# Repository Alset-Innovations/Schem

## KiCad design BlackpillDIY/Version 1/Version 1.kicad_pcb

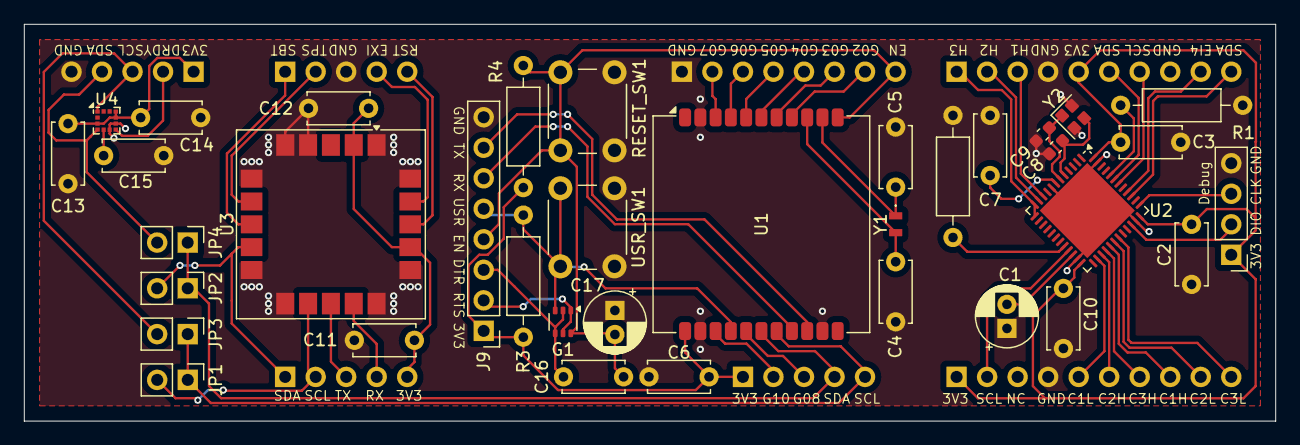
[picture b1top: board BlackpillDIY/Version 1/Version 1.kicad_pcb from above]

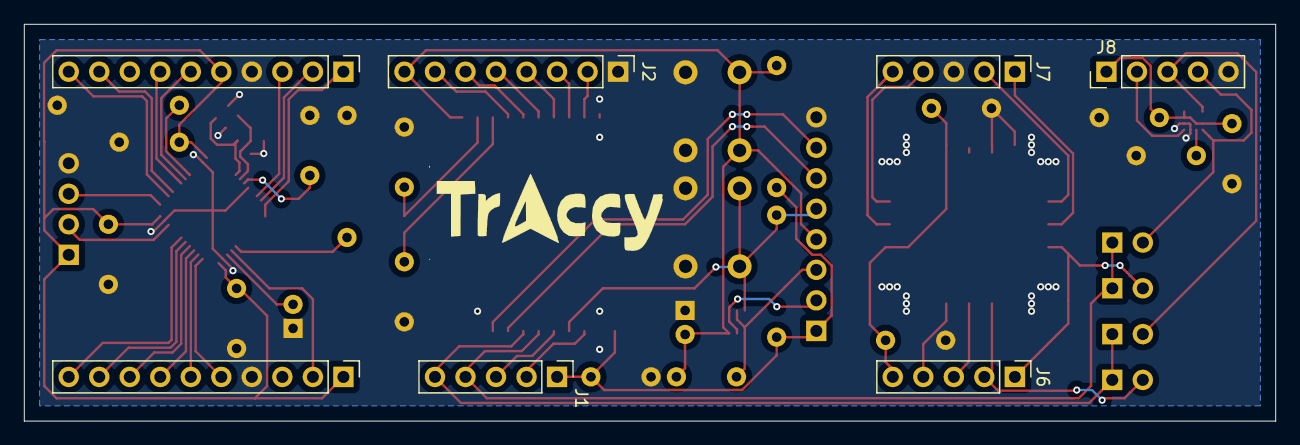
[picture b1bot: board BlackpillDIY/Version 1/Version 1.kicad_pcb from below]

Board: 2 copper layers, 104.1 x 33.0 mm, 43 parts (7 on the bottom side), 57 nets.

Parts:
C1, C2, C3, C6, C7, C11, C12, C13, C14, C15, C16: 100n; C_Disc_D5.0mm_W2.5mm_P5.00mm
C4, C5: 22p; C_Disc_D5.0mm_W2.5mm_P5.00mm
C8, C9: 12p; C_0603_1608Metric
C10, C17: 2.2u; CP_Radial_D5.0mm_P2.00mm
G1: 2N7002BKS; SOT-363_SC-70-6
J1: Conn_01x08; PinHeader_1x05_P2.54mm_Vertical
J2, J9: Conn_01x08; PinHeader_1x08_P2.54mm_Vertical
J3: Debug; PinHeader_1x04_P2.54mm_Vertical
J4: Left Header; PinHeader_1x10_P2.54mm_Vertical
J5: Right Header; PinHeader_1x10_P2.54mm_Vertical
J6, J7, J8: Conn_01x05; PinHeader_1x05_P2.54mm_Vertical
JP1, JP2, JP3, JP4: Jumper_2_Open; PinHeader_1x02_P2.54mm_Vertical
R1, R2, R3, R4: 10k; R_Axial_DIN0207_L6.3mm_D2.5mm_P10.16mm_Horizontal
RESET_SW1: RESET_SW; SW_PUSH_6mm_H4.3mm
U1: HT-CT62; Heltec_HT-CT62
U2: STM32F411CCUx; QFN-48-1EP_7x7mm_P0.5mm_EP5.6x5.6mm
U3: SAM-M8Q; ublox_SAM-M8Q
U4: LIS2MDL; LGA-12_2x2mm_P0.5mm
USR_SW1: RESET_SW; SW_PUSH_6mm_H4.3mm
Y1: LFXTAL062558Reel
Y2: Crystal_GND24; Crystal_SMD_SeikoEpson_FA128-4Pin_2.0x1.6mm

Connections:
+3.3V1: C1.1, C2.1, C3.1, J3.1, J4.5, J5.1, U2.24 (VDD), U2.36 (VDD), U2.48 (VDD)
+3.3V2: C6.1, J1.1, J9.1, R3.2, R4.1, U1.12 (VDD)
+3.3V3: C11.1, C12.1, J6.5, U3.2 (VCC_IO), U3.17 (VCC)
+3.3V4: C13.1, C14.1, J8.1, U4.3 (~CS), U4.9 (Vdd), U4.10 (Vdd_IO)
/BOOT0: R1.2, U2.44 (BOOT0)
/BOOT1: R2.2, U2.20 (PB2)
/C1: C15.1, U4.5 (C1)
/DTR: C16.1, G1.2 (Gate_1), G1.4 (Source_2), J9.3
/ESPEN: C16.2, C17.2, G1.6 (Drain_1), J2.8, J9.4, R4.2, RESET_SW1.2 (B), U1.11 (EN)
/EXTINT: J7.4, U3.19 (EXTINT)
/GPIO0: C5.1, U1.10 (GPIO0), Y1.1
/GPIO1: C4.1, U1.9 (GPIO1), Y1.2 (CRYSTAL_2)
/GPIO2: J2.7, U1.8 (GPIO2)
/GPIO3: J2.6, U1.7 (GPIO3)
/GPIO4: J2.5, U1.6 (GPIO4)
/GPIO5: J2.4, U1.5 (GPIO5)
/GPIO6: J2.3, U1.4 (GPIO6)
/GPIO7: J2.2, U1.3 (GPIO7)
/GPIO8: J1.3, U1.16 (GPIO8)
/GPIO10: J1.2, U1.14 (GPIO10)
/RCC_IN: C8.2, U2.5 (PH0), Y2.3
/RCC_OUT: C9.2, U2.6 (PH1), Y2.1
/RS: C7.2, U2.7 (NRST)
/RST: J7.5, U3.18 (~RESET)
/RTS: G1.1 (Source_1), G1.5 (Gate_2), J9.2
/RX: J9.6, U1.19 (GPIO20_RXD)
/RXD: J6.4, U3.14 (RXD)
/SBOOT: J7.1, U3.8 (~SAFEBOOT)
/SCL: J1.5, JP1.1 (A), JP3.1 (A), U1.18 (GPIO19_DP)
/SCL1: J6.2, JP1.2 (B), U3.12 (SCL)
/SCL2: J8.3, JP3.2 (B), U4.1 (SCL/SPC)
/SDA: J1.4, JP2.1 (A), JP4.1 (A), U1.17 (GPIO18_DN)
/SDA1: J6.1, JP2.2 (B), U3.9 (SDA)
/SDA2: J8.4, JP4.2 (B), U4.4 (SDA/SDI/SDO)
/SWCLK: J3.3, U2.37 (PA14)
/SWDIO: J3.2, U2.34 (PA13)
/TPULSE: J7.2, U3.7 (TIMEPULSE)
/TX: J9.7, U1.20 (GPIO21_TXD)
/TXD: J6.3, U3.13 (TXD)
/USR_Key: G1.3 (Drain_2), J9.5, R3.1, U1.15 (GPIO9), USR_SW1.2 (B)
/VCAP: C10.2, U2.22 (VCAP1)
DRDY: J8.2, U4.7 (DRDY)
EXTI4: J4.9, U2.40 (PB4)
GND: C1.2, C2.2, C3.2, C4.2, C5.2, C6.2, C7.1, C8.1, C9.1, C10.1, C11.2, C12.2, C13.2, C14.2, C15.2, C17.1, J2.1, J3.4, J4.4, J5.4, J7.3, J8.5, J9.8, R1.1, R2.1, RESET_SW1.1 (A), U1.2 (GND), U1.13 (GND), U1.21 (GND), U2.8 (VSSA), U2.23 (VSS), U2.35 (VSS), U2.47 (VSS), U2.49 (VSS), U3.1 (GND), U3.4 (GND), U3.5 (GND), U3.6 (GND), U3.10 (GND), U3.11 (GND), U3.15 (GND), U3.16 (GND), U3.20 (GND), U4.6 (GND), U4.8 (GND), USR_SW1.1 (A), Y2.2, Y2.4
I2C1_SCL: J4.7, U2.42 (PB6)
I2C1_SDA: J4.6, U2.43 (PB7)
I2C2_SCL: J5.2, U2.21 (PB10)
I2C2_SDA: J4.10, U2.39 (PB3)
TIM1_CH1: J5.8, U2.29 (PA8)
TIM1_CH1N: J5.5, U2.26 (PB13)
TIM1_CH2: J5.9, U2.30 (PA9)
TIM1_CH2N: J5.6, U2.27 (PB14)
TIM1_CH3: J5.10, U2.31 (PA10)
TIM1_CH3N: J5.7, U2.28 (PB15)
TIM2_CH1: J4.3, U2.10 (PA0)
TIM2_CH2: J4.2, U2.11 (PA1)
TIM2_CH3: J4.1, U2.12 (PA2), U2.13 (PA3)

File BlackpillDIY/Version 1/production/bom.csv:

Designator,Footprint,Quantity,Value,LCSC Part #
"C1, C11, C12, C13, C14, C15, C16, C2, C3, C6, C7",C_Disc_D5.0mm_W2.5mm_P5.00mm,11,100n,
"C10, C17",CP_Radial_D5.0mm_P2.00mm,2,2.2u,
"C4, C5",C_Disc_D5.0mm_W2.5mm_P5.00mm,2,22p,
"C8, C9",0603,2,12p,
G1,SOT-363_SC-70-6,1,2N7002BKS,
J1,PinHeader_1x05_P2.54mm_Vertical,1,Conn_01x08,
"J2, J9",PinHeader_1x08_P2.54mm_Vertical,2,Conn_01x08,
J3,PinHeader_1x04_P2.54mm_Vertical,1,Debug,
J4,PinHeader_1x10_P2.54mm_Vertical,1,Left Header,
J5,PinHeader_1x10_P2.54mm_Vertical,1,Right Header,
"J6, J7, J8",PinHeader_1x05_P2.54mm_Vertical,3,Conn_01x05,
"R1, R2, R3, R4",R_Axial_DIN0207_L6.3mm_D2.5mm_P10.16mm_Horizontal,4,10k,
"RST_SW1, USR_SW1",SW_PUSH_6mm_H4.3mm,2,RESET_SW,
U1,Heltec_HT-CT62,1,HT-CT62,
U2,QFN-48-1EP_7x7mm_P0.5mm_EP5.6x5.6mm,1,STM32F411CCUx,
U3,ublox_SAM-M8Q,1,SAM-M8Q,
U4,LGA-12_2x2mm_P0.5mm,1,LIS2MDL,
Y1,LFXTAL062558Reel,1,LFXTAL062558Reel,
Y2,Crystal_SMD_SeikoEpson_FA128-4Pin_2.0x1.6mm,1,Crystal_GND24,

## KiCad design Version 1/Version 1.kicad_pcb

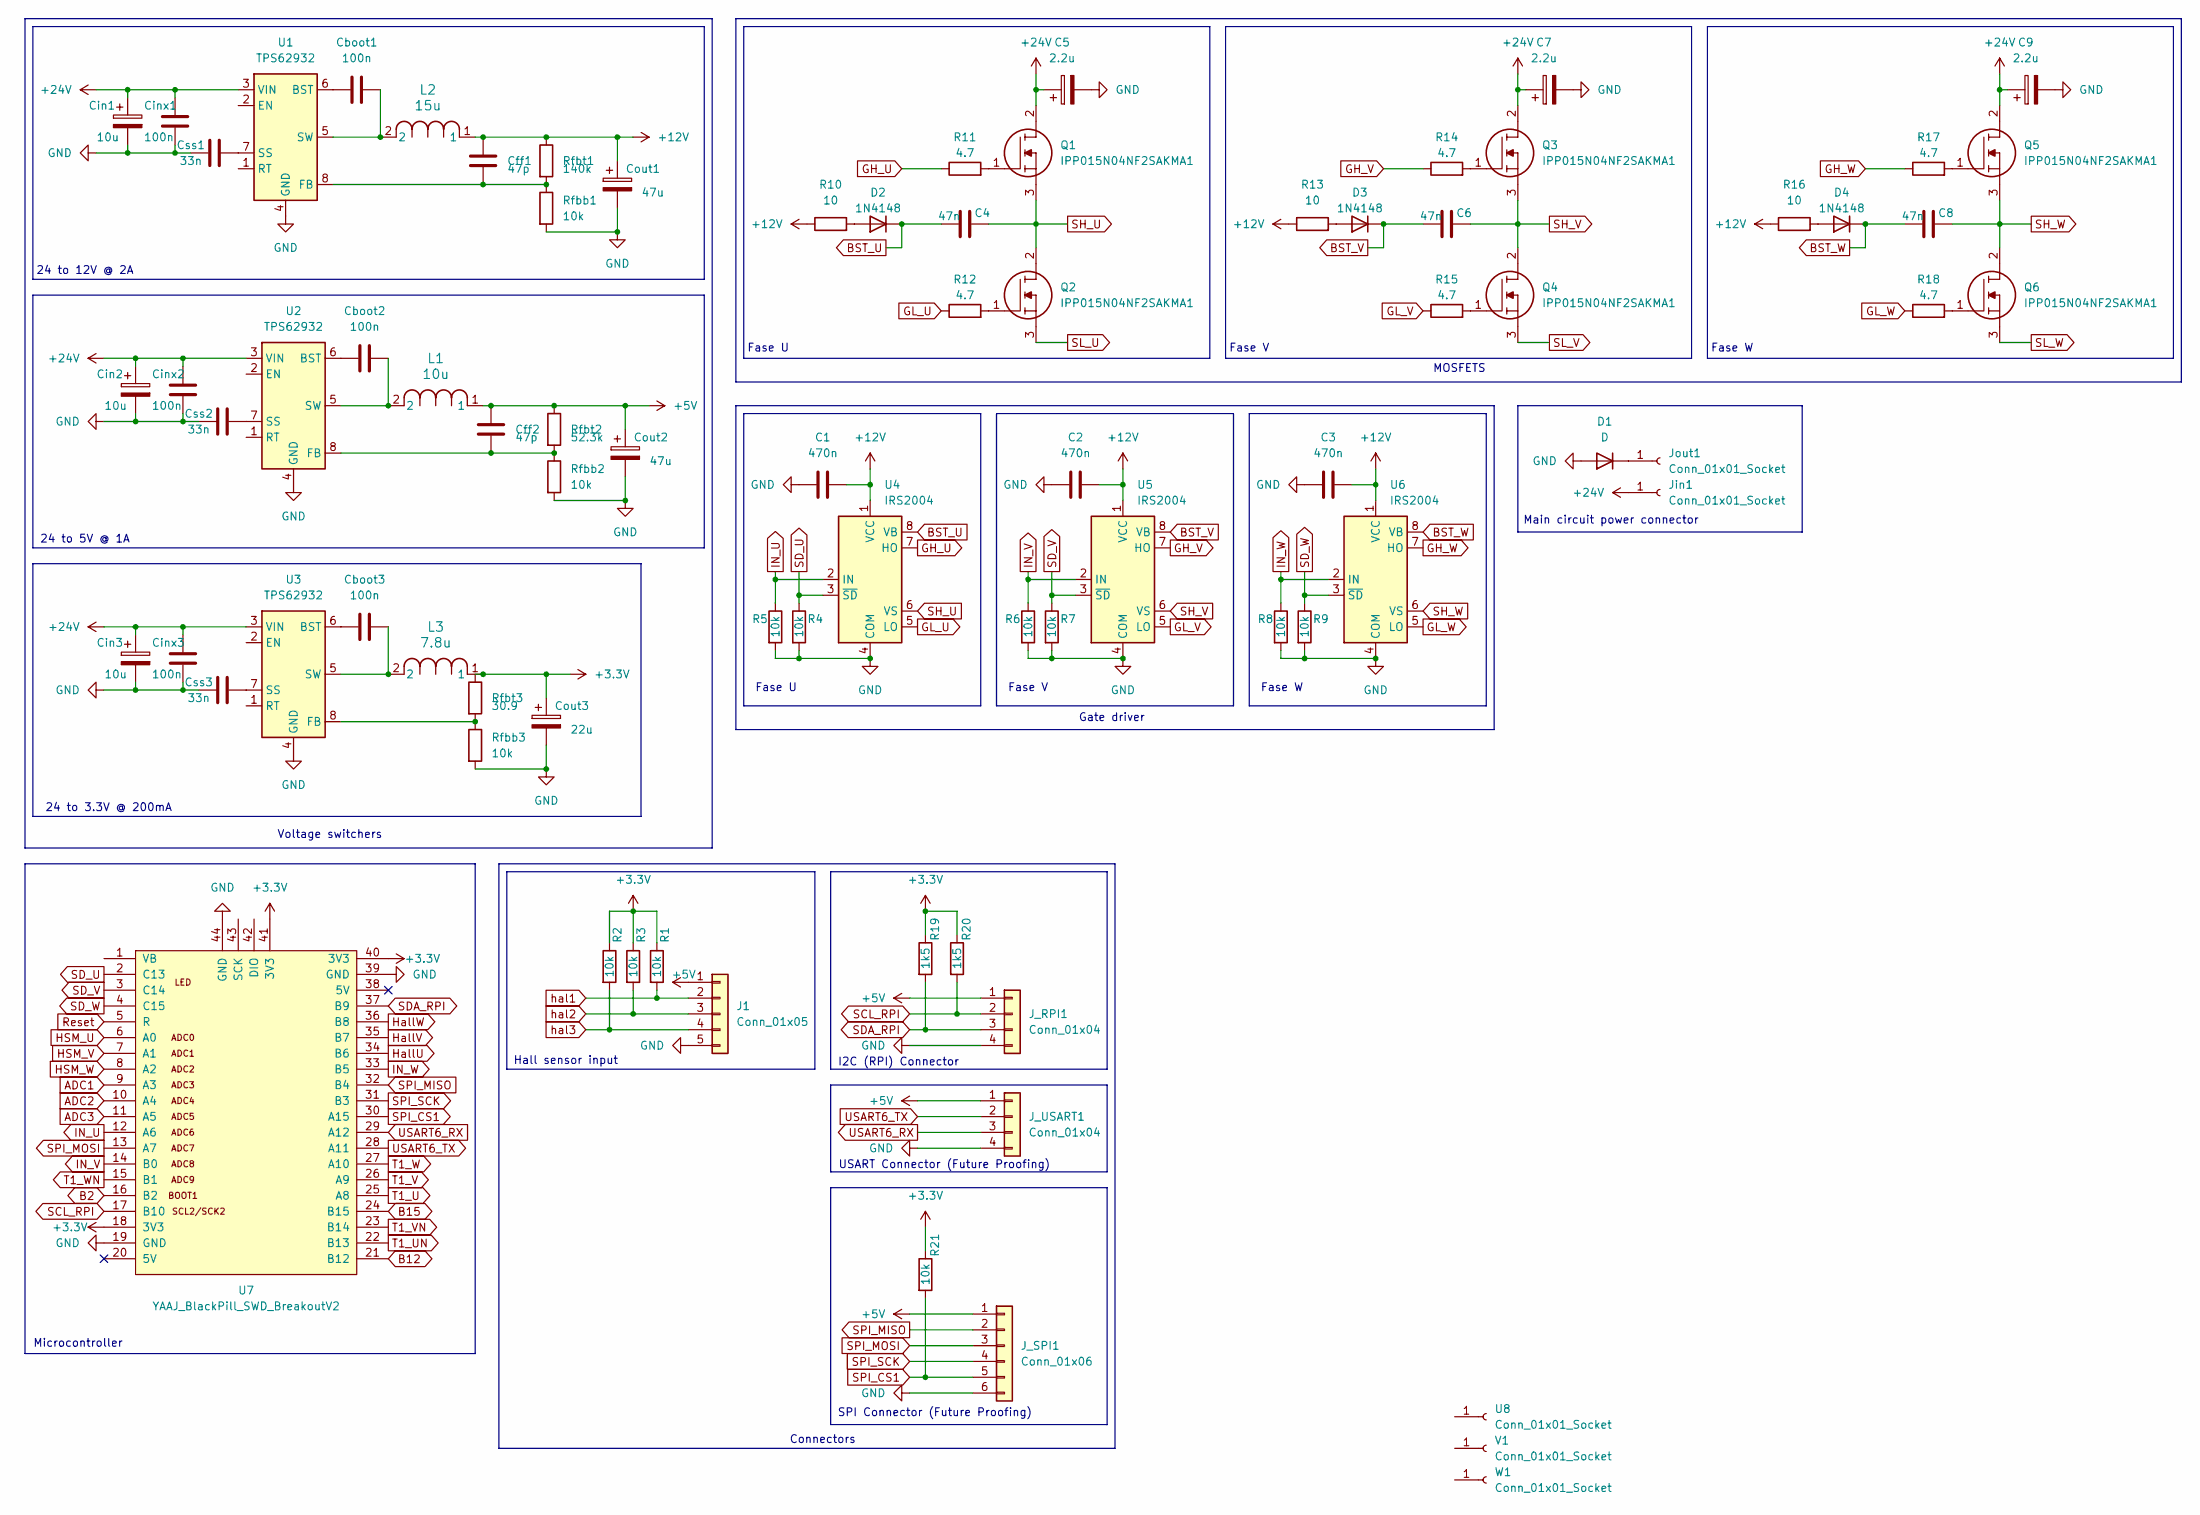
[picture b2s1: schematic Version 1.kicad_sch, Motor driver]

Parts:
C1, C2, C3: 470n; C_Disc_D3.4mm_W2.1mm_P2.50mm
C4, C6, C8: 47n; C_Disc_D3.4mm_W2.1mm_P2.50mm
C5, C7, C9: 2.2u; CP_Radial_D5.0mm_P2.50mm
Cboot1, Cboot2, Cboot3: 100n; C_Disc_D3.4mm_W2.1mm_P2.50mm
Cff1, Cff2: 47p; C_Disc_D3.4mm_W2.1mm_P2.50mm
Cin1, Cin2, Cin3: 10u; CP_Radial_D5.0mm_P2.50mm
Cinx1, Cinx2, Cinx3: 100n; C_Disc_D3.4mm_W2.1mm_P2.50mm
Cout1, Cout2: 47u; CP_Radial_D12.5mm_P5.00mm
Cout3: 22u; CP_Radial_D12.5mm_P5.00mm
Css1, Css2, Css3: 33n; C_Disc_D3.4mm_W2.1mm_P2.50mm
D1: D; D_DO-34_SOD68_P12.70mm_Horizontal
D2, D3, D4: 1N4148; D_DO-35_SOD27_P7.62mm_Horizontal
J1: Conn_01x05; PinHeader_1x05_P1.27mm_Vertical
J_RPI1: Conn_01x04; PinHeader_1x04_P1.27mm_Vertical
J_SPI1: Conn_01x06; PinHeader_1x06_P1.27mm_Vertical
J_USART1: Conn_01x04; PinHeader_1x04_P1.27mm_Vertical
Jin1: Conn_01x01_Socket; MountingHole_4.3mm_M4_DIN965_Pad
Jout1: Conn_01x01_Socket; MountingHole_4.3mm_M4_DIN965_Pad
L1: 10u; L_Axial_L13.0mm_D4.5mm_P7.62mm_Vertical_Fastron_HCCC
L2: 15u; L_Axial_L13.0mm_D4.5mm_P7.62mm_Vertical_Fastron_HCCC
L3: 7.8u; L_Axial_L13.0mm_D4.5mm_P7.62mm_Vertical_Fastron_HCCC
Q1, Q2, Q3, Q4, Q5, Q6: IPP015N04NF2SAKMA1; TO254P475X1028X1996-3P; Mouser Part Number 726-IPP015N04NF2SAKM
R1, R2, R3, R4, R5, R6, R7, R8, R9, R21: 10k; R_Axial_DIN0207_L6.3mm_D2.5mm_P10.16mm_Horizontal
R10, R13, R16: 10; R_Axial_DIN0207_L6.3mm_D2.5mm_P10.16mm_Horizontal
R11, R12, R14, R15, R17, R18: 4.7; R_Axial_DIN0207_L6.3mm_D2.5mm_P10.16mm_Horizontal
R19, R20: 1k5; R_Axial_DIN0207_L6.3mm_D2.5mm_P10.16mm_Horizontal
Rfbb1, Rfbb2, Rfbb3: 10k; R_Axial_DIN0207_L6.3mm_D2.5mm_P10.16mm_Horizontal
Rfbt1: 140k; R_Axial_DIN0207_L6.3mm_D2.5mm_P10.16mm_Horizontal
Rfbt2: 52.3k; R_Axial_DIN0207_L6.3mm_D2.5mm_P10.16mm_Horizontal
Rfbt3: 30.9; R_Axial_DIN0207_L6.3mm_D2.5mm_P10.16mm_Horizontal
U1, U2, U3: TPS62932; SOT-583-8
U4, U5, U6: IRS2004; DIP762W56P254L988H533Q8N
U7: YAAJ_BlackPill_SWD_BreakoutV2; Blackpill
U8: Conn_01x01_Socket; MountingHole_4.3mm_M4_DIN965_Pad
V1: Conn_01x01_Socket; MountingHole_4.3mm_M4_DIN965_Pad
W1: Conn_01x01_Socket; MountingHole_4.3mm_M4_DIN965_Pad

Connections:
+3.3V: Cout3.1, L3.1, R1.1, R2.1, R3.1, R19.1, R20.1, R21.1, Rfbt3.1, U7.18 (3V3), U7.40 (3V3), U7.41 (3V3)
+5V: Cff2.1, Cout2.1, J1.1, J_RPI1.1, J_SPI1.1, J_USART1.1, L1.1, Rfbt2.1
+12V: C1.2, C2.2, C3.2, Cff1.1, Cout1.1, L2.1, R10.1, R13.1, R16.1, Rfbt1.1, U4.1 (VCC), U5.1 (VCC), U6.1 (VCC)
+24V: C5.1, C7.1, C9.1, Cin1.1, Cin2.1, Cin3.1, Cinx1.1, Cinx2.1, Cinx3.1, Jin1.1, Q1.2, Q3.2, Q5.2, U1.3 (VIN), U2.3 (VIN), U3.3 (VIN)
ADC1: U7.9 (A3)
ADC2: U7.10 (A4)
ADC3: U7.11 (A5)
B2: U7.16 (B2)
B12: U7.21 (B12)
B15: U7.24 (B15)
BST_U: C4.1, D2.1 (K), U4.8 (VB)
BST_V: C6.1, D3.1 (K), U5.8 (VB)
BST_W: C8.1, D4.1 (K), U6.8 (VB)
GH_U: R11.1, U4.7 (HO)
GH_V: R14.1, U5.7 (HO)
GH_W: R17.1, U6.7 (HO)
GL_U: R12.1, U4.5 (LO)
GL_V: R15.1, U5.5 (LO)
GL_W: R18.1, U6.5 (LO)
GND: C1.1, C2.1, C3.1, C5.2, C7.2, C9.2, Cin1.2, Cin2.2, Cin3.2, Cinx1.2, Cinx2.2, Cinx3.2, Cout1.2, Cout2.2, Cout3.2, Css1.1, Css2.1, Css3.1, D1.2 (A), J1.5, J_RPI1.4, J_SPI1.6, J_USART1.4, R4.2, R5.2, R6.2, R7.2, R8.2, R9.2, Rfbb1.2, Rfbb2.2, Rfbb3.2, U1.4 (GND), U2.4 (GND), U3.4 (GND), U4.4 (COM), U5.4 (COM), U6.4 (COM), U7.19 (GND), U7.39 (GND), U7.44 (GND)
HSM_U: U7.6 (A0)
HSM_V: U7.7 (A1)
HSM_W: U7.8 (A2)
HallU: U7.34 (B6)
HallV: U7.35 (B7)
HallW: U7.36 (B8)
IN_U: R5.1, U4.2 (IN), U7.12 (A6)
IN_V: R6.1, U5.2 (IN), U7.14 (B0)
IN_W: R8.1, U6.2 (IN), U7.33 (B5)
unnamed: D1.1 (K), Jout1.1
unnamed: D2.2 (A), R10.2
unnamed: D3.2 (A), R13.2
unnamed: D4.2 (A), R16.2
unnamed: Q1.1, R11.2
unnamed: Q2.1, R12.2
unnamed: Q3.1, R14.2
unnamed: Q4.1, R15.2
unnamed: Q5.1, R17.2
unnamed: Q6.1, R18.2
unnamed: Cboot1.1, U1.6 (BST)
unnamed: Cff1.2, Rfbb1.1, Rfbt1.2, U1.8 (FB)
unnamed: Css1.2, U1.7 (SS)
unnamed: Cboot1.2, L2.2, U1.5 (SW)
unnamed: Cboot2.1, U2.6 (BST)
unnamed: Cff2.2, Rfbb2.1, Rfbt2.2, U2.8 (FB)
unnamed: Css2.2, U2.7 (SS)
unnamed: Cboot2.2, L1.2, U2.5 (SW)
unnamed: Cboot3.1, U3.6 (BST)
unnamed: Rfbb3.1, Rfbt3.2, U3.8 (FB)
unnamed: Css3.2, U3.7 (SS)
unnamed: Cboot3.2, L3.2, U3.5 (SW)
Reset: U7.5 (R)
SCL_RPI: J_RPI1.2, R20.2, U7.17 (B10)
SDA_RPI: J_RPI1.3, R19.2, U7.37 (B9)
SD_U: R4.1, U4.3 (~SD), U7.2 (C13)
SD_V: R7.1, U5.3 (~SD), U7.3 (C14)
SD_W: R9.1, U6.3 (~SD), U7.4 (C15)
SH_U: C4.2, Q1.3, Q2.2, U4.6 (VS)
SH_V: C6.2, Q3.3, Q4.2, U5.6 (VS)
SH_W: C8.2, Q5.3, Q6.2, U6.6 (VS)
SL_U: Q2.3
SL_V: Q4.3
SL_W: Q6.3
SPI_CS1: J_SPI1.5, R21.2, U7.30 (A15)
SPI_MISO: J_SPI1.2, U7.32 (B4)
SPI_MOSI: J_SPI1.3, U7.13 (A7)
SPI_SCK: J_SPI1.4, U7.31 (B3)
T1_U: U7.25 (A8)
T1_UN: U7.22 (B13)
T1_V: U7.26 (A9)
T1_VN: U7.23 (B14)
T1_W: U7.27 (A10)
T1_WN: U7.15 (B1)
USART6_RX: J_USART1.3, U7.29 (A12)
USART6_TX: J_USART1.2, U7.28 (A11)
hal1: J1.2, R1.2
hal2: J1.3, R3.2
hal3: J1.4, R2.2

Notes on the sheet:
Voltage switchers
24 to 12V @ 2A
Gate driver
Fase W
Microcontroller
Fase V
Fase U
I2C (RPI) Connector
SPI Connector (Future Proofing)
Main circuit power connector
24 to 5V @ 1A
Connectors
USART Connector (Future Proofing)
Hall sensor input
24 to 3.3V @ 200mA
MOSFETS

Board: 2 copper layers, 82 parts (0 on the bottom side), 56 nets, no tracks yet.

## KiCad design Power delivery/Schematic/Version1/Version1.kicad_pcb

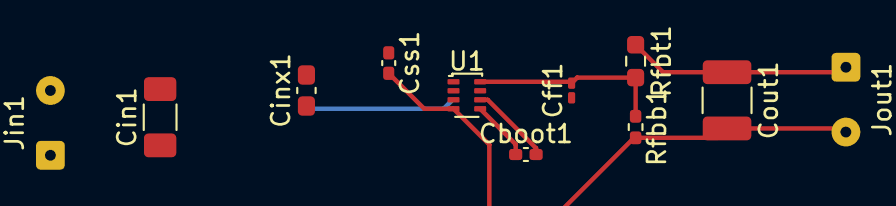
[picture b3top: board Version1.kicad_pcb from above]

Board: 2 copper layers, 11 parts (0 on the bottom side), 7 nets.

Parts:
Cboot1: 100nF; C_0402_1005Metric_Pad0.74x0.62mm_HandSolder
Cff1: 47p; C_0201_0603Metric_Pad0.64x0.40mm_HandSolder
Cin1: 10u; C_1206_3216Metric_Pad1.33x1.80mm_HandSolder
Cinx1: 100n; C_0603_1608Metric_Pad1.08x0.95mm_HandSolder
Cout1: 47u; C_1210_3225Metric_Pad1.33x2.70mm_HandSolder
Css1: 33n; C_0402_1005Metric_Pad0.74x0.62mm_HandSolder
Jin1: Conn_01x02; SolderWire-0.1sqmm_1x02_P3.6mm_D0.4mm_OD1mm
Jout1: Conn_01x02; SolderWire-0.1sqmm_1x02_P3.6mm_D0.4mm_OD1mm
Rfbb1: 10k; R_0402_1005Metric_Pad0.72x0.64mm_HandSolder
Rfbt1: 140k; R_0603_1608Metric_Pad0.98x0.95mm_HandSolder
U1: TPS62932; SOT-583-8

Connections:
+12V: Cout1.1, Jout1.1, Rfbt1.1
+24V: Cin1.1, Cinx1.1, Jin1.1, U1.3 (VIN)
GND: Cin1.2, Cinx1.2, Cout1.2, Css1.2, Jin1.2, Jout1.2, Rfbb1.2, U1.4 (GND)
unnamed: Cboot1.2, U1.6 (BST)
unnamed: Cff1.2, Rfbb1.1, Rfbt1.2, U1.8 (FB)
unnamed: Css1.1, U1.7 (SS)
unnamed: Cboot1.1, U1.5 (SW)

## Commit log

2024-02-07 added start
2024-02-08 added hal sensor data
2024-02-09 Files from my current schematic
2024-02-11 Added DRV8302
2024-02-15 added extra regulators
2024-02-15 added regulatorIC
2024-02-15 done
2024-02-20 added more info
2024-03-01 updated some schem files
2024-03-02 updated schem
2024-03-03 updated circuit
2024-03-03 added 3D models
2024-03-03 latest 3d components
2024-03-11 udpated pcb
2024-03-12 Added Connectors SPI and USART
2024-03-12 Last few changes
    Renamed a connector and added proper layout to the schematic.
2024-03-13 updated footprints and added pos in pcb design
2024-03-15 updated SCHEMATIC
2024-03-19 stuff
2024-03-19 added altium
2024-03-19 miep
2024-03-21 Nothing
    Nothing
2024-03-21 added V regulated switching
2024-03-21 added gate driver
2024-03-22 added gate drivers
2024-03-24 added STM32
2024-03-24 added
2024-03-28 added PCB
2024-03-28 Final
2024-03-28 added connector for hall
2024-04-11 notin
    nothing
2024-04-11 Components added to Buck. Furthmore nothing changed
2024-04-16 miauw
2024-04-16 added current measure
2024-04-16 added addr bits
2024-04-16 added current sensing circuit
2024-04-17 components added to converter
2024-04-17 De up-to-date versie
2024-04-17 up-to-date
2024-04-17 Created new Project file, because of Constraint manager
2024-04-25 updated altium docs
2024-04-29 adde d3d
2024-04-29 adde renmdrs
2024-05-09 Added everything according to official schem
2024-05-09 Created THT PCB
2024-05-09 renders
2024-05-11 Added breakouts for ESP Ublock and LIS.
2024-05-14 Added silkscreen and autoboot for esp
2024-05-15 board breaks
2024-05-15 loelioe
2024-05-30 Changed to a single breadboard capable PCB
2024-05-30 Added latest Gerbers
2024-05-30 Unimportant
